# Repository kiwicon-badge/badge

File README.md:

# Kiwicon Intro to Badge Hacking

This repo is to host the instructions and code for the Kiwicon 2038 Intro to Badge Hacking course (https://www.kiwicon.org/the-con/training/intro-to-badge-hacking/).

## Welcome!

First up, welcome to the course :D

I hope that today is enjoyable and that you leave having gained skills and knowledge you can put to good use.

Learning the basics of electronics is a great skill. You may use this in the future to deconstructe IOT devices, build your own tools, or simply to fix a broken gadget. When combined with basic programming skills, this can take on a whole new level, where your imagination and, usually more importantly, budget are the only limits!

In particular, learning about how microcontrollers work is a great asset. This gives you the fundamentals for learning about more complex computers and systems. Note that, these days, a computer isn't really a single entity, it is a whole ecosystem of various smaller microcontrollers doing all sorts of functions. Your laptops itself likely has several dozen 'computers' in it, the CPU, GPU, controllers for the keyboard, touchpad, webcam, touchbar, SSD, Wi-Fi, Bluetooth... not to mention dongles. It's a great time to get a better understanding of how all these components can interact, particularly in light of recent events!

There is no fixed timeline to today. I have broken everything down into labs which we will move through, but feel free to go at your own pace! The only aim that I have for you today is to leave with a completed, working badge. So take time to make sure you understand everything and get the most out of it. If you race through everything, take the time to help out those around you or come up with some new idea you can program the badge to do, it's up to you.

Happy hacking!

## Safety / Conduct

+ In the event of a fire, leave all your gear and follow the exit signs out of the building.
+ In the event of an earthquake, go under your table. When the shaking stops, egress the building following the exit signs, and move to clear ground (up near parliament).
+ We will be working with toxic elements, i.e. lead (PB), in the solder. Do not ingest the solder and make sure you wash your hands before eating anything.
+ The solder flux may be irritating to some. If you have an issue, move to one of the tables / stations nearer the windows.
+ Soldering irons are hot! Always beware where you are putting it and make sure the cord is in a safe location where noone can trip over it.
+ If you see any hazards, let me know and we will work to minimise or remedy these.
+ We follow the [Kiwicon Code of Conduct](https://www.kiwicon.org/faq/#q9). Don't be a shitweasel! We're here to learn in a collaborative environment. Leave everything else at the door.

## Breaks / Facilities

+ Please note this is a working environment. Please keep noise down outside the conference room!
+ There is cans of Sprite in the fridge, water in the tap.
+ Toilets are in the stairwells, female toilets are to the left just outside the door, males to the left on the other side of the single lift. Ask for an access card before you leave, as the stairwell doors are locked. If you get locked out without a card, go to the ground floor and take the lift back up to level 4.
+ We will take regular breaks, but if you have something to do, feel free to bounce in and out as needed.

## Course Labs

+ Electrical Circuits - https://github.com/kiwicon-badge/badge/tree/master/lab-01
+ Microcontrollers - https://github.com/kiwicon-badge/badge/tree/master/lab-02
+ Loading a Program - https://github.com/kiwicon-badge/badge/tree/master/lab-03
+ Soldering - https://github.com/kiwicon-badge/badge/tree/master/lab-04
+ Badge Assembly - https://github.com/kiwicon-badge/badge/tree/master/lab-05
+ Badge Programming / Hacking - https://github.com/kiwicon-badge/badge/tree/master/lab-06

After that, if anyone is interested, we can run through PCB design using Eagle (and maybe Fritzing).

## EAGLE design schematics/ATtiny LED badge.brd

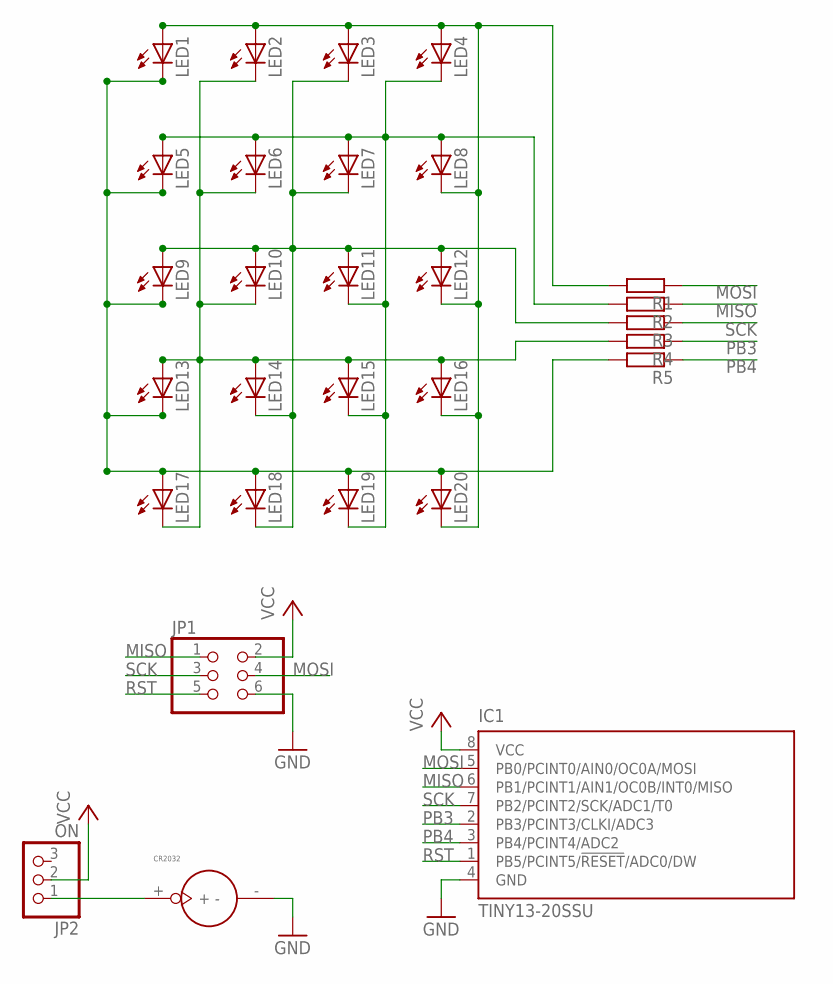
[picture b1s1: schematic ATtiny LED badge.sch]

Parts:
CR2032: BATTERY_1236_C
IC1: TINY13-20SSU; 8S1
JP1: PINHD-2X3; 2X03
JP2: ON; 1X03
LED1, LED2, LED3, LED4, LED5, LED6, LED7, LED8, LED9, LED10, LED11, LED12, LED13, LED14, LED15, LED16, LED17, LED18, LED19, LED20: LED3MM
R1, R2, R3, R4, R5: R-EU_0207/7; 0207/7

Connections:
GND: CR2032.-, IC1.4 (GND), JP1.6
MISO: IC1.6 (PB1/PCINT1/AIN1/OC0B/INT0/MISO), JP1.1, R2.1
MOSI: IC1.5 (PB0/PCINT0/AIN0/OC0A/MOSI), JP1.4, R1.1
unnamed: LED1.A, LED2.A, LED3.A, LED4.A, LED8.K (C), LED12.K (C), LED16.K (C), LED20.K (C), R1.2
unnamed: LED4.K (C), LED5.A, LED6.A, LED7.A, LED8.A, LED11.K (C), LED15.K (C), LED19.K (C), R2.2
unnamed: LED3.K (C), LED7.K (C), LED9.A, LED10.A, LED11.A, LED12.A, LED14.K (C), LED18.K (C), R3.2
unnamed: LED2.K (C), LED6.K (C), LED10.K (C), LED13.A, LED14.A, LED15.A, LED16.A, LED17.K (C), R4.2
unnamed: LED1.K (C), LED5.K (C), LED9.K (C), LED13.K (C), LED17.A, LED18.A, LED19.A, LED20.A, R5.2
unnamed: CR2032.+, JP2.1
PB3: IC1.2 (PB3/PCINT3/CLKI/ADC3), R4.1
PB4: IC1.3 (PB4/PCINT4/ADC2), R5.1
RST: IC1.1 (PB5/PCINT5/!RESET!/ADC0/DW), JP1.5
SCK: IC1.7 (PB2/PCINT2/SCK/ADC1/T0), JP1.3, R3.1
VCC: IC1.8 (VCC), JP1.2, JP2.2

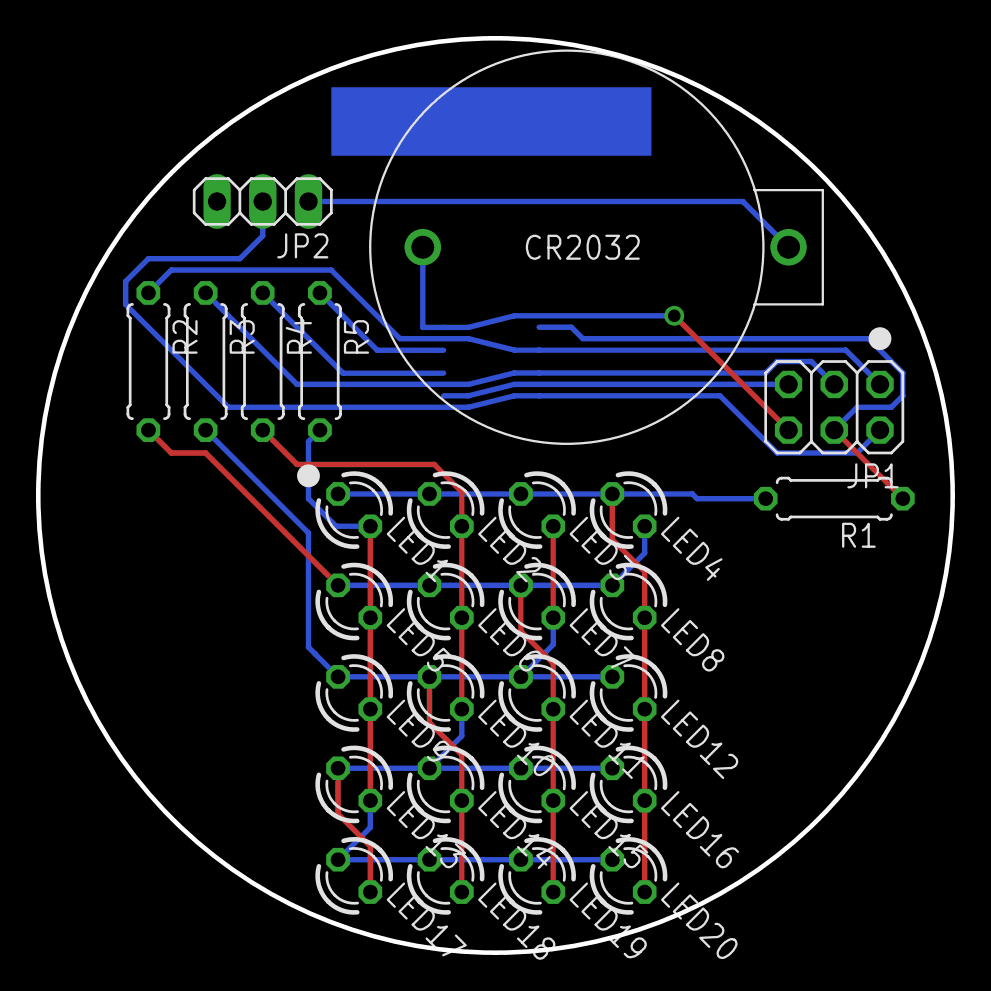
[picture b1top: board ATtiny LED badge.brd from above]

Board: 2 copper layers, 50.8 x 50.8 mm, 29 parts (1 on the bottom side), 14 nets.

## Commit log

2018-10-02 Create compile script.
2018-10-02 Fixed executable calls.
2018-10-02 Initial commit.
2018-10-02 Changed filetype to markdown
2018-10-02 Fixed formatting.
2018-10-02 Finally fixed formatting.
2018-10-02 Ironed out some kinks.
2018-10-02 Create test
2018-10-03 Added section titles
2018-10-03 Added content
2018-10-29 Expanded content.
2018-10-30 Added content.
2018-10-30 Additional content.
2018-11-08 Changed filename.
2018-11-08 Rename kiwicon.c to kiwicon.ino
2018-11-08 Create deletethis
2018-11-08 Add files via upload
    Design file for Kiwicon badge.
2018-11-08 Rename scrolling.c to scrolling.ino
2018-11-08 Rename sequential_characters.c to sequential_characters.ino
2018-11-13 Create testfile
2018-11-13 Changed to support two pins.
2018-11-13 Rename attiny13a_blink.ino.txt to attiny13a_blink.ino
